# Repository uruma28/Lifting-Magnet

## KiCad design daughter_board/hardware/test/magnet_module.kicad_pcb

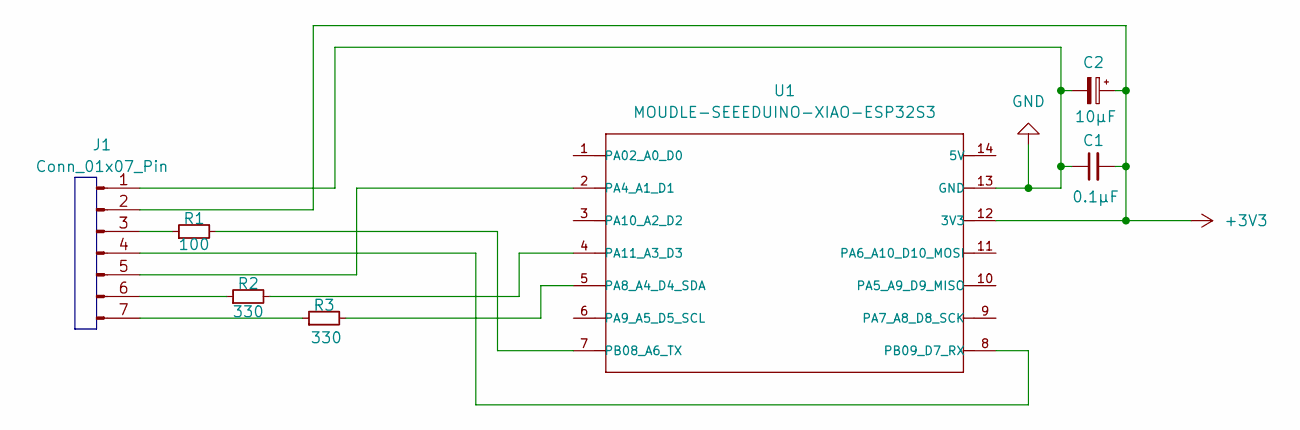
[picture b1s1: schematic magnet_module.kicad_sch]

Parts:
C1: 0.1μF; C_Radial_D6.3mm_H5.0mm_P2.50mm
C2: 10μF; CP_Radial_D5.0mm_P2.50mm
J1: Conn_01x07_Pin; PinHeader_1x07_P2.54mm_Vertical
R1: 100; R_Axial_DIN0207_L6.3mm_D2.5mm_P10.16mm_Horizontal
R2, R3: 330; R_Axial_DIN0207_L6.3mm_D2.5mm_P10.16mm_Horizontal
U1: MOUDLE-SEEEDUINO-XIAO-ESP32S3; XIAO-ESP32S3-DIP

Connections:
+3V3: C1.2, C2.1, J1.2, U1.12 (3V3)
GND: C1.1, C2.2, J1.1, U1.13 (GND)
unnamed: J1.3, R1.1
unnamed: J1.4, U1.8 (PB09_D7_RX)
unnamed: J1.5, U1.2 (PA4_A1_D1)
unnamed: J1.6, R2.1
unnamed: J1.7, R3.1
unnamed: R3.2, U1.5 (PA8_A4_D4_SDA)
unnamed: R2.2, U1.4 (PA11_A3_D3)
unnamed: R1.2, U1.7 (PB08_A6_TX)

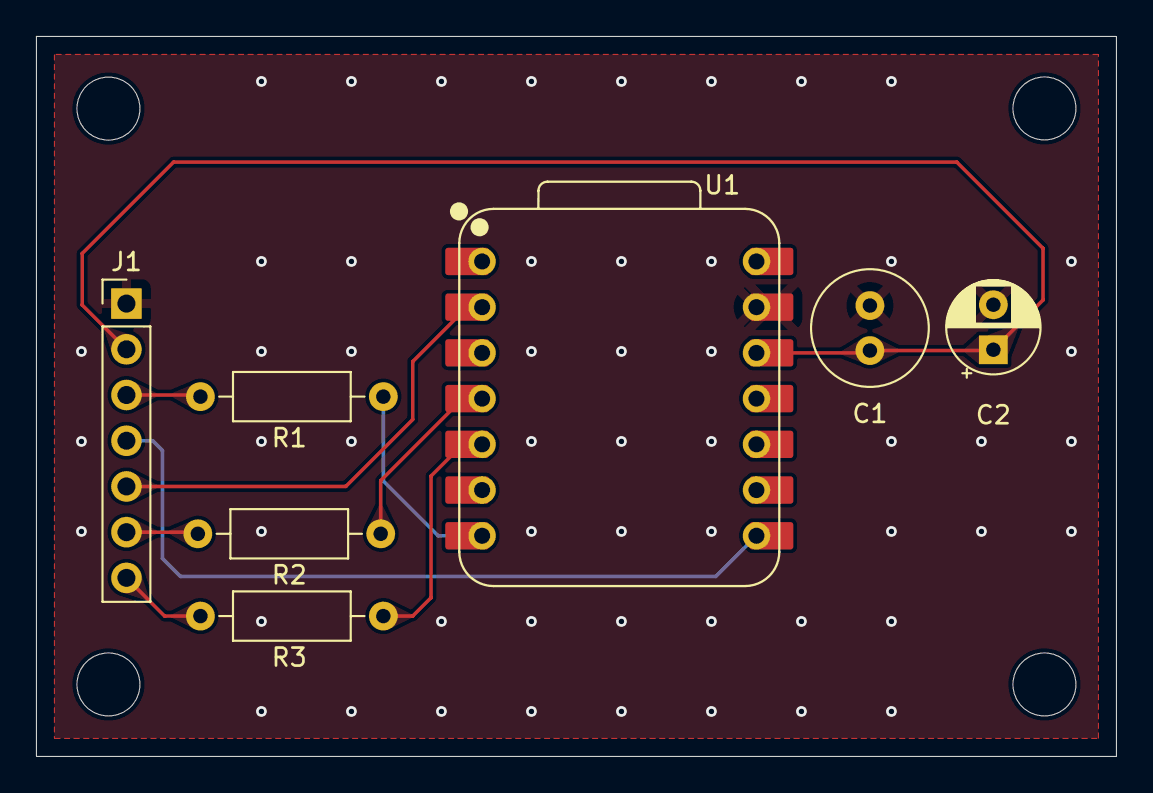
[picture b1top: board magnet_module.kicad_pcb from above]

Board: 2 copper layers, 60.0 x 40.0 mm, 7 parts (0 on the bottom side), 10 nets.

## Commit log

2025-06-03 プロジェクト初期セットアップ
